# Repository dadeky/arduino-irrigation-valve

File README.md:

# arduino-irrigation-valve
C++ project for arduino - controling the solenoid valve
New project

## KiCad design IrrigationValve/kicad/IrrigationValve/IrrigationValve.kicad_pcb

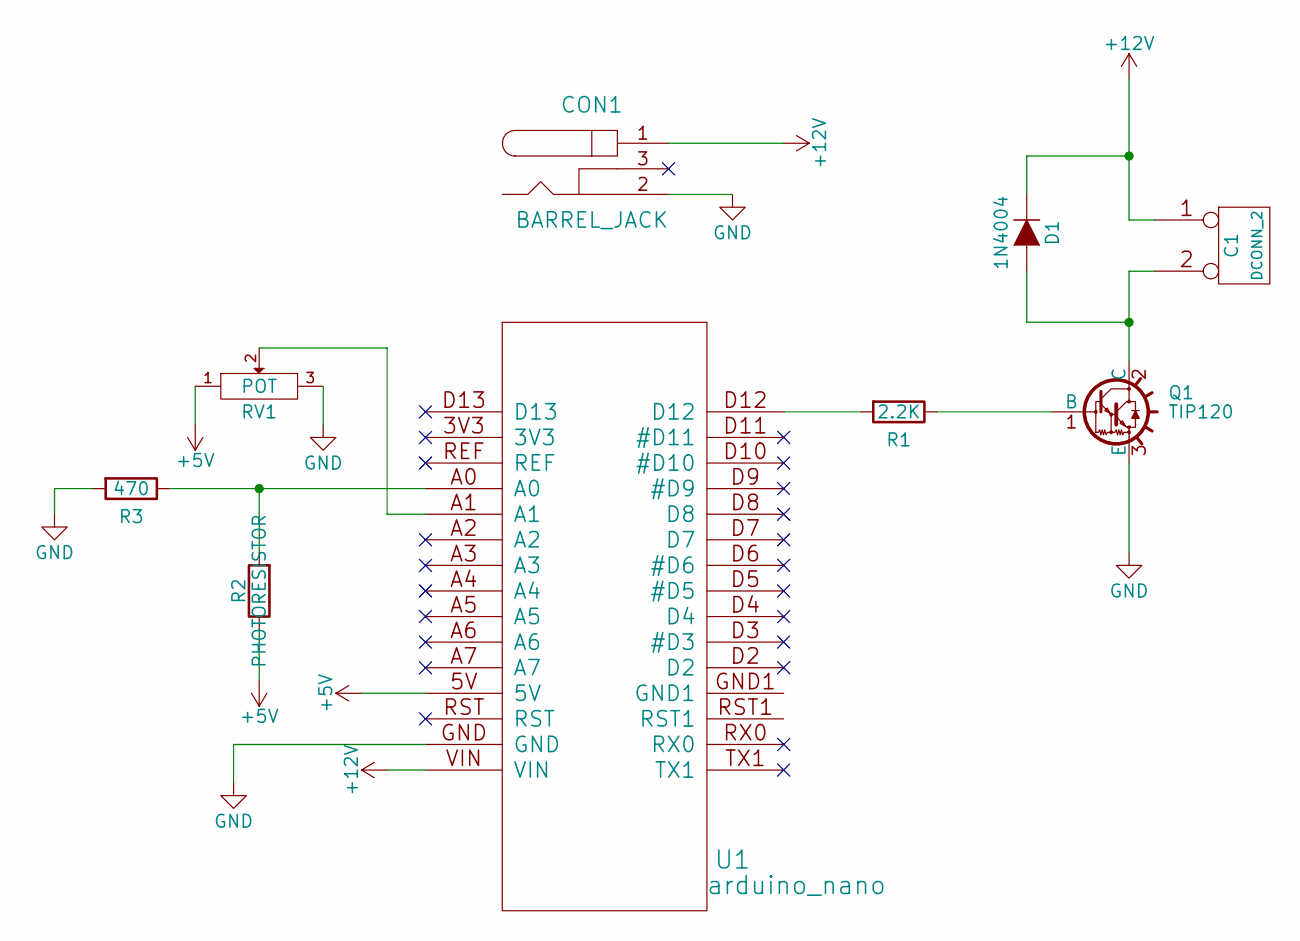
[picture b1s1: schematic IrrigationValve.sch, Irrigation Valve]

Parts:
C1: DCONN_2; AK300-2
CON1: BARREL_JACK
D1: 1N4004; Diode_DO-201AD_Horizontal_RM15
Q1: TIP120; TO-220
R1: 2.2K; Resistor_Vertical_RM5mm
R2: PHOTORESISTOR; Resistor_Vertical_RM5mm
R3: 470; Resistor_Vertical_RM5mm
RV1: POT; Potentiometer_Alps-RK16-single
U1: arduino_nano

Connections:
+5V: R2.1, RV1.1, U1.5V
+12V: C1.1, CON1.1, D1.1 (K), U1.VIN
GND: CON1.2, Q1.3 (E), R3.2, RV1.3, U1.GND
unnamed: C1.2, D1.2 (A), Q1.2 (C)
unnamed: Q1.1 (B), R1.1
unnamed: R1.2, U1.D12
unnamed: R2.2, R3.1, U1.A0
unnamed: RV1.2, U1.A1

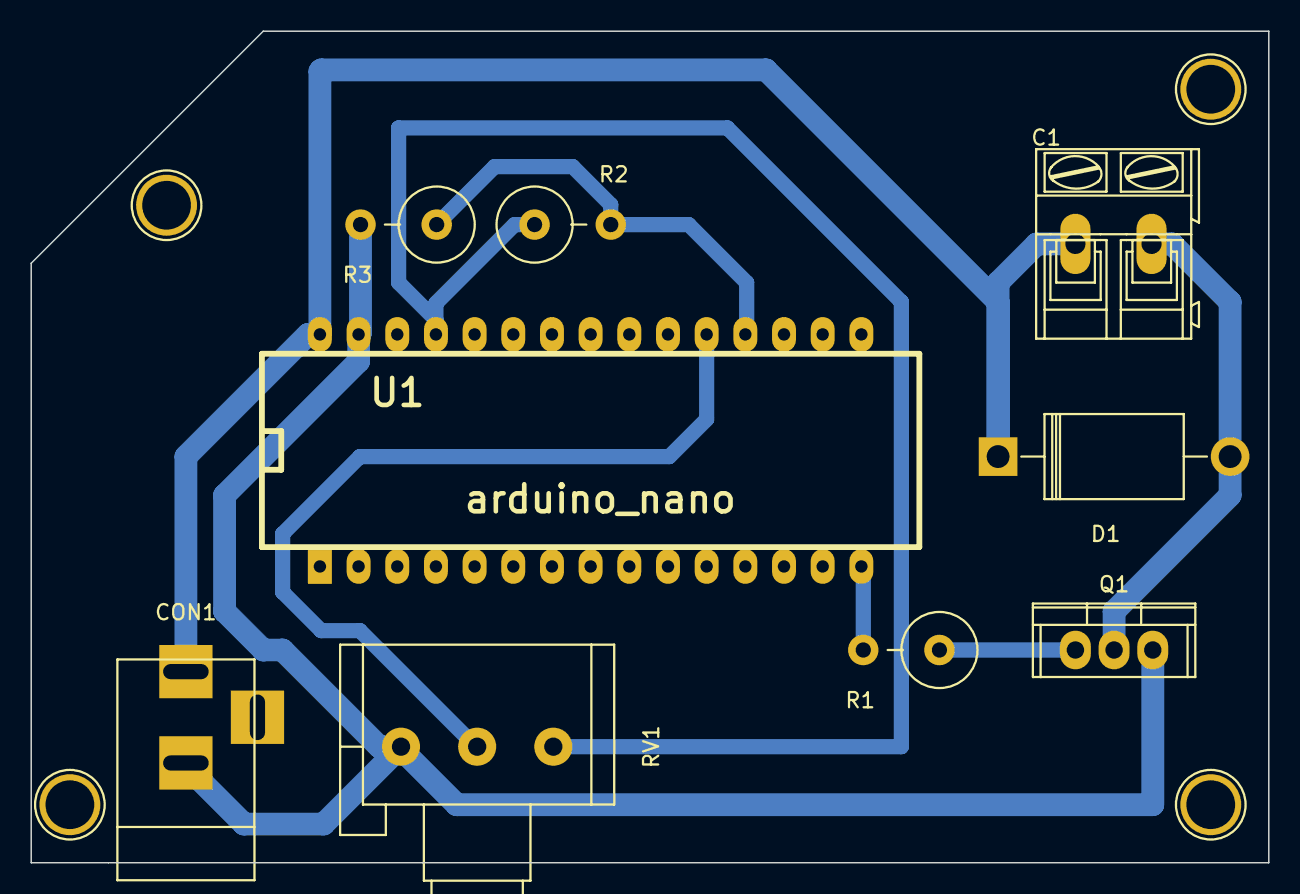
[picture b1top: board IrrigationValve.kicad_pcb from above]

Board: 2 copper layers, 81.3 x 54.6 mm, 13 parts (0 on the bottom side), 8 nets.

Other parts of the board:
Mount: 1pin
Mount#2, Mount#3, Mount#4: 1pin

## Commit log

2017-12-28 new sloeber version
2018-01-05 kicad
2018-01-08 One too many include.
2018-06-22 Some
2018-07-12 Photon
